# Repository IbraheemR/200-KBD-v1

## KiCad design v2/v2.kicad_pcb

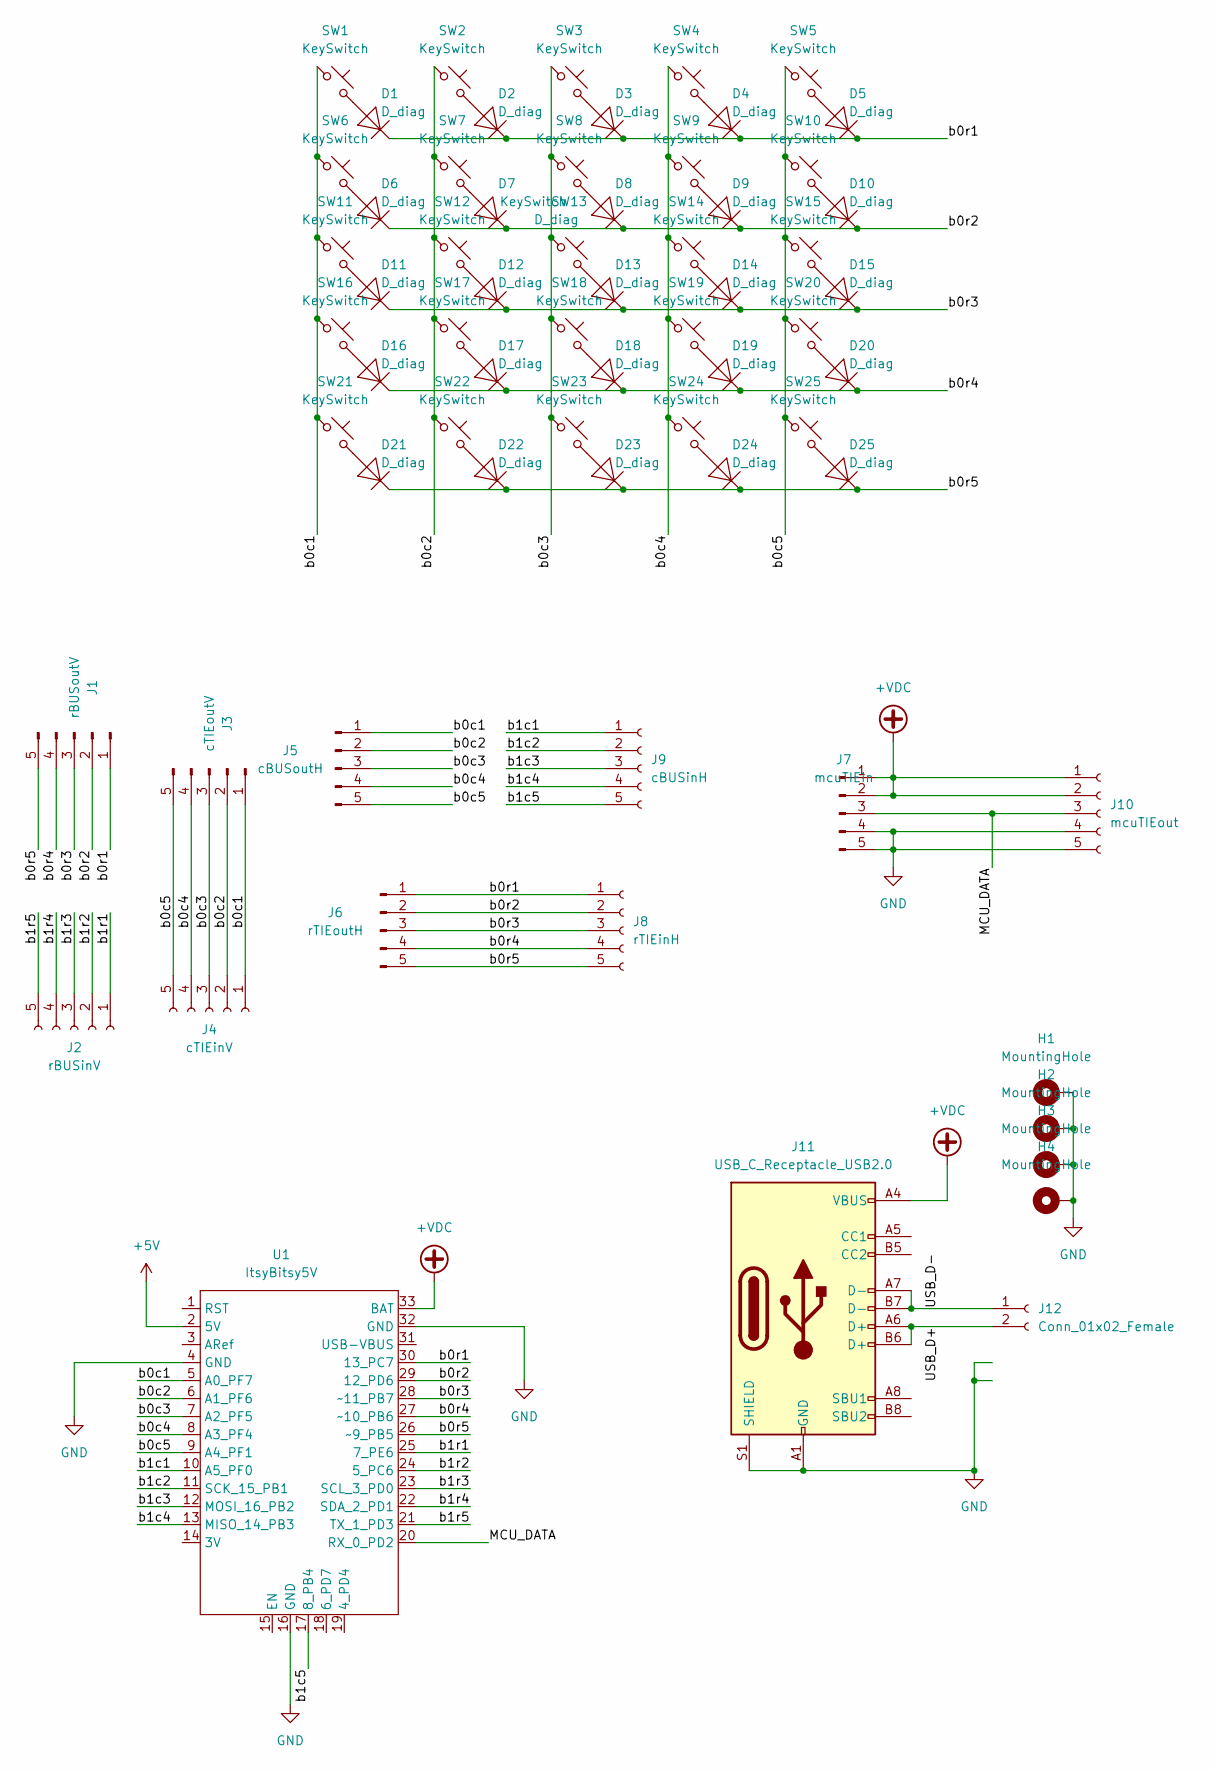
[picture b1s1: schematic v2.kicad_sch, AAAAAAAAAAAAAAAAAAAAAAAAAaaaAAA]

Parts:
D1, D2, D3, D4, D5, D6, D7, D8, D9, D10, D11, D12, D13, D14, D15, D16, D17, D18, D19, D20, D21, D22, D23, D24, D25: D_diag; D_SOD-123_NoSilk
H1, H2, H3, H4: MountingHole; MountingHole_Screw_2.5mm
J1: rBUSoutV; DumbEdgeConnectorHorizontal
J2: rBUSinV; DumbEdgeConnectorHorizontal
J3: cTIEoutV; DumbEdgeConnectorHorizontal
J4: cTIEinV; DumbEdgeConnectorHorizontal
J5: cBUSoutH; DumbEdgeConnectorVertical
J6: rTIEoutH; DumbEdgeConnectorVertical
J7: mcuTIEin; DumbEdgeConnectorVertical
J8: rTIEinH; DumbEdgeConnectorVertical
J9: cBUSinH; DumbEdgeConnectorVertical
J10: mcuTIEout; DumbEdgeConnectorVertical
J11: USB_C_Receptacle_USB2.0; USB_C_Receptacle_XKB_U262-16XN-4BVC11_NoSilk
J12: Conn_01x02_Female; USB_JUMP_PAD
SW1, SW2, SW3, SW4, SW5, SW6, SW7, SW8, SW9, SW10, SW11, SW12, SW13, SW14, SW15, SW16, SW17, SW18, SW19, SW20, SW21, SW22, SW23, SW24, SW25: KeySwitch; GateronLowProfileKeyswitch
U1: ItsyBitsy5V; ItsyBitsy

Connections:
+5V: U1.2 (5V)
+VDC: J7.1, J7.2, J10.1, J10.2, J11.A4 (VBUS), J11.A9 (VBUS), J11.B4 (VBUS), J11.B9 (VBUS), U1.33 (BAT)
/MCU_DATA: J7.3, J10.3, U1.20 (RX_0_PD2)
/USB_D+: J11.A6 (D+), J11.B6 (D+), J12.2
/USB_D-: J11.A7 (D-), J11.B7 (D-), J12.1
/b0c1: J3.1, J4.1, J5.1, SW1.1, SW6.1, SW11.1, SW16.1, SW21.1, U1.5 (A0_PF7)
/b0c2: J3.2, J4.2, J5.2, SW2.1, SW7.1, SW12.1, SW17.1, SW22.1, U1.6 (A1_PF6)
/b0c3: J3.3, J4.3, J5.3, SW3.1, SW8.1, SW13.1, SW18.1, SW23.1, U1.7 (A2_PF5)
/b0c4: J3.4, J4.4, J5.4, SW4.1, SW9.1, SW14.1, SW19.1, SW24.1, U1.8 (A3_PF4)
/b0c5: J3.5, J4.5, J5.5, SW5.1, SW10.1, SW15.1, SW20.1, SW25.1, U1.9 (A4_PF1)
/b0r1: D1.2, D2.2, D3.2, D4.2, D5.2, J1.1, J6.1, J8.1, U1.30 (13_PC7)
/b0r2: D6.2, D7.2, D8.2, D9.2, D10.2, J1.2, J6.2, J8.2, U1.29 (12_PD6)
/b0r3: D11.2, D12.2, D13.2, D14.2, D15.2, J1.3, J6.3, J8.3, U1.28 (~11_PB7)
/b0r4: D16.2, D17.2, D18.2, D19.2, D20.2, J1.4, J6.4, J8.4, U1.27 (~10_PB6)
/b0r5: D21.2, D22.2, D23.2, D24.2, D25.2, J1.5, J6.5, J8.5, U1.26 (~9_PB5)
/b1c1: J9.1, U1.10 (A5_PF0)
/b1c2: J9.2, U1.11 (SCK_15_PB1)
/b1c3: J9.3, U1.12 (MOSI_16_PB2)
/b1c4: J9.4, U1.13 (MISO_14_PB3)
/b1c5: J9.5, U1.17 (8_PB4)
/b1r1: J2.1, U1.25 (7_PE6)
/b1r2: J2.2, U1.24 (5_PC6)
/b1r3: J2.3, U1.23 (SCL_3_PD0)
/b1r4: J2.4, U1.22 (SDA_2_PD1)
/b1r5: J2.5, U1.21 (TX_1_PD3)
GND: H1.1, H2.1, H3.1, H4.1, J7.4, J7.5, J10.4, J10.5, J11.A1 (GND), J11.A12 (GND), J11.B1 (GND), J11.B12 (GND), J11.S1 (SHIELD), U1.4 (GND), U1.16 (GND), U1.32 (GND)
unnamed: D1.1, SW1.2
unnamed: D2.1, SW2.2
unnamed: D3.1, SW3.2
unnamed: D4.1, SW4.2
unnamed: D5.1, SW5.2
unnamed: D6.1, SW6.2
unnamed: D7.1, SW7.2
unnamed: D8.1, SW8.2
unnamed: D9.1, SW9.2
unnamed: D10.1, SW10.2
unnamed: D11.1, SW11.2
unnamed: D12.1, SW12.2
unnamed: D13.1, SW13.2
unnamed: D14.1, SW14.2
unnamed: D15.1, SW15.2
unnamed: D16.1, SW16.2
unnamed: D17.1, SW17.2
unnamed: D18.1, SW18.2
unnamed: D19.1, SW19.2
unnamed: D20.1, SW20.2
unnamed: D21.1, SW21.2
unnamed: D22.1, SW22.2
unnamed: D23.1, SW23.2
unnamed: D24.1, SW24.2
unnamed: D25.1, SW25.2

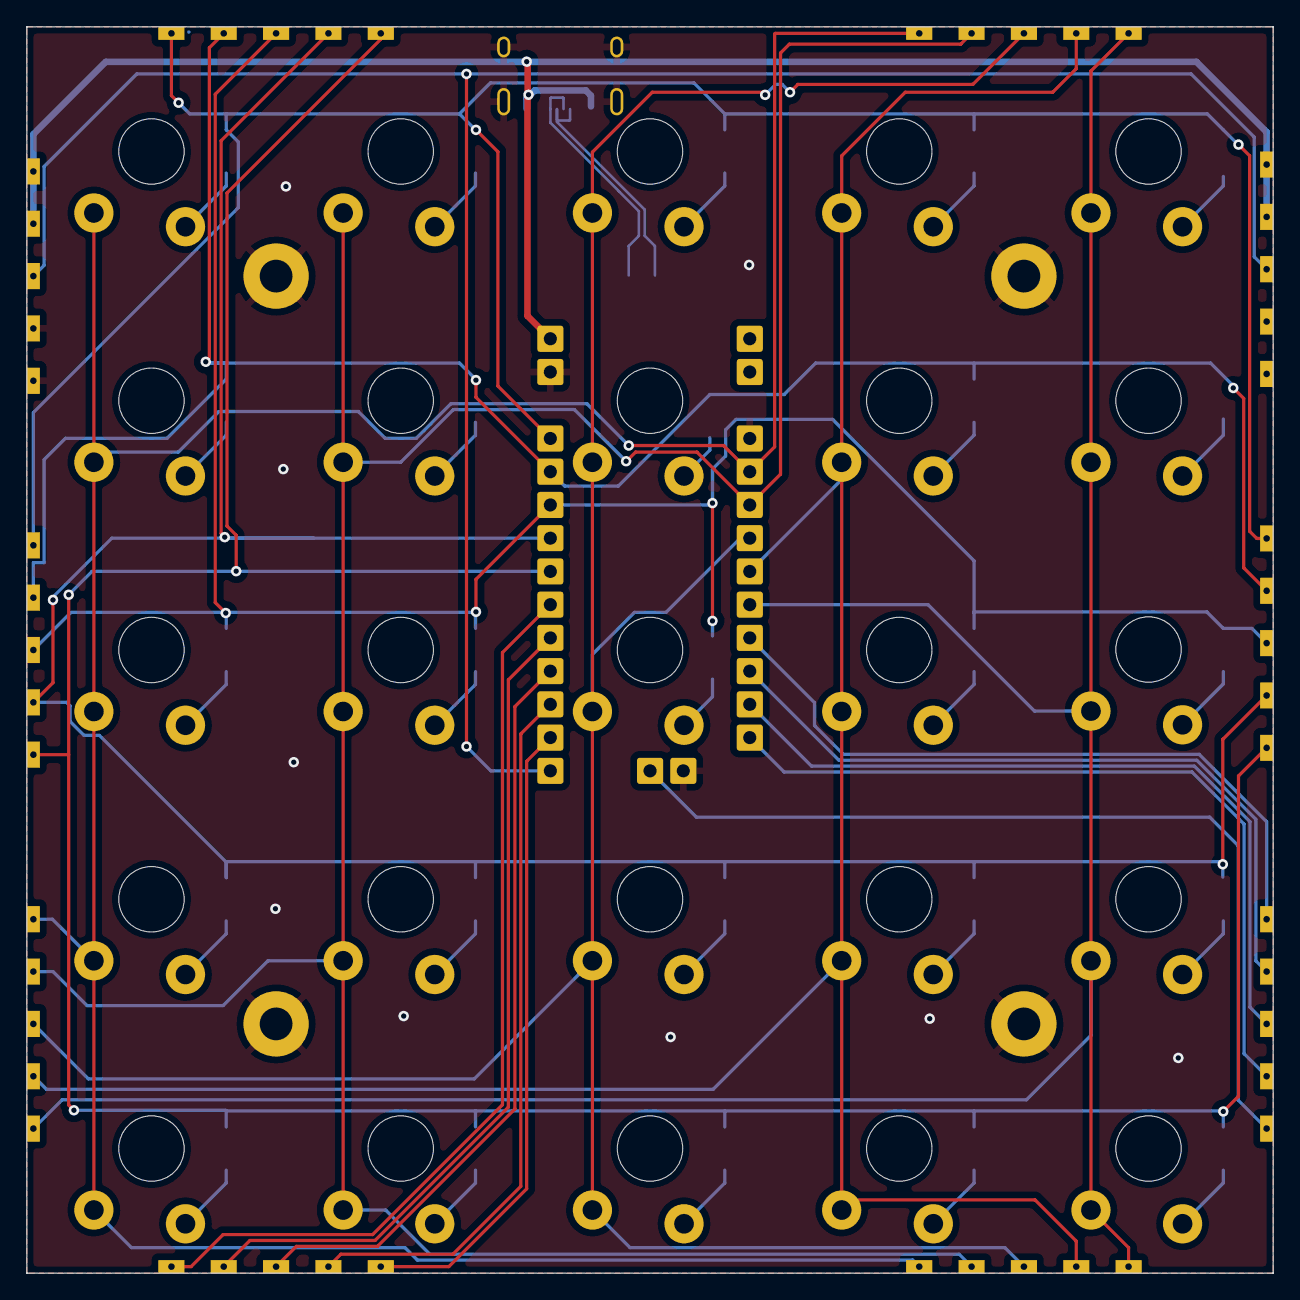
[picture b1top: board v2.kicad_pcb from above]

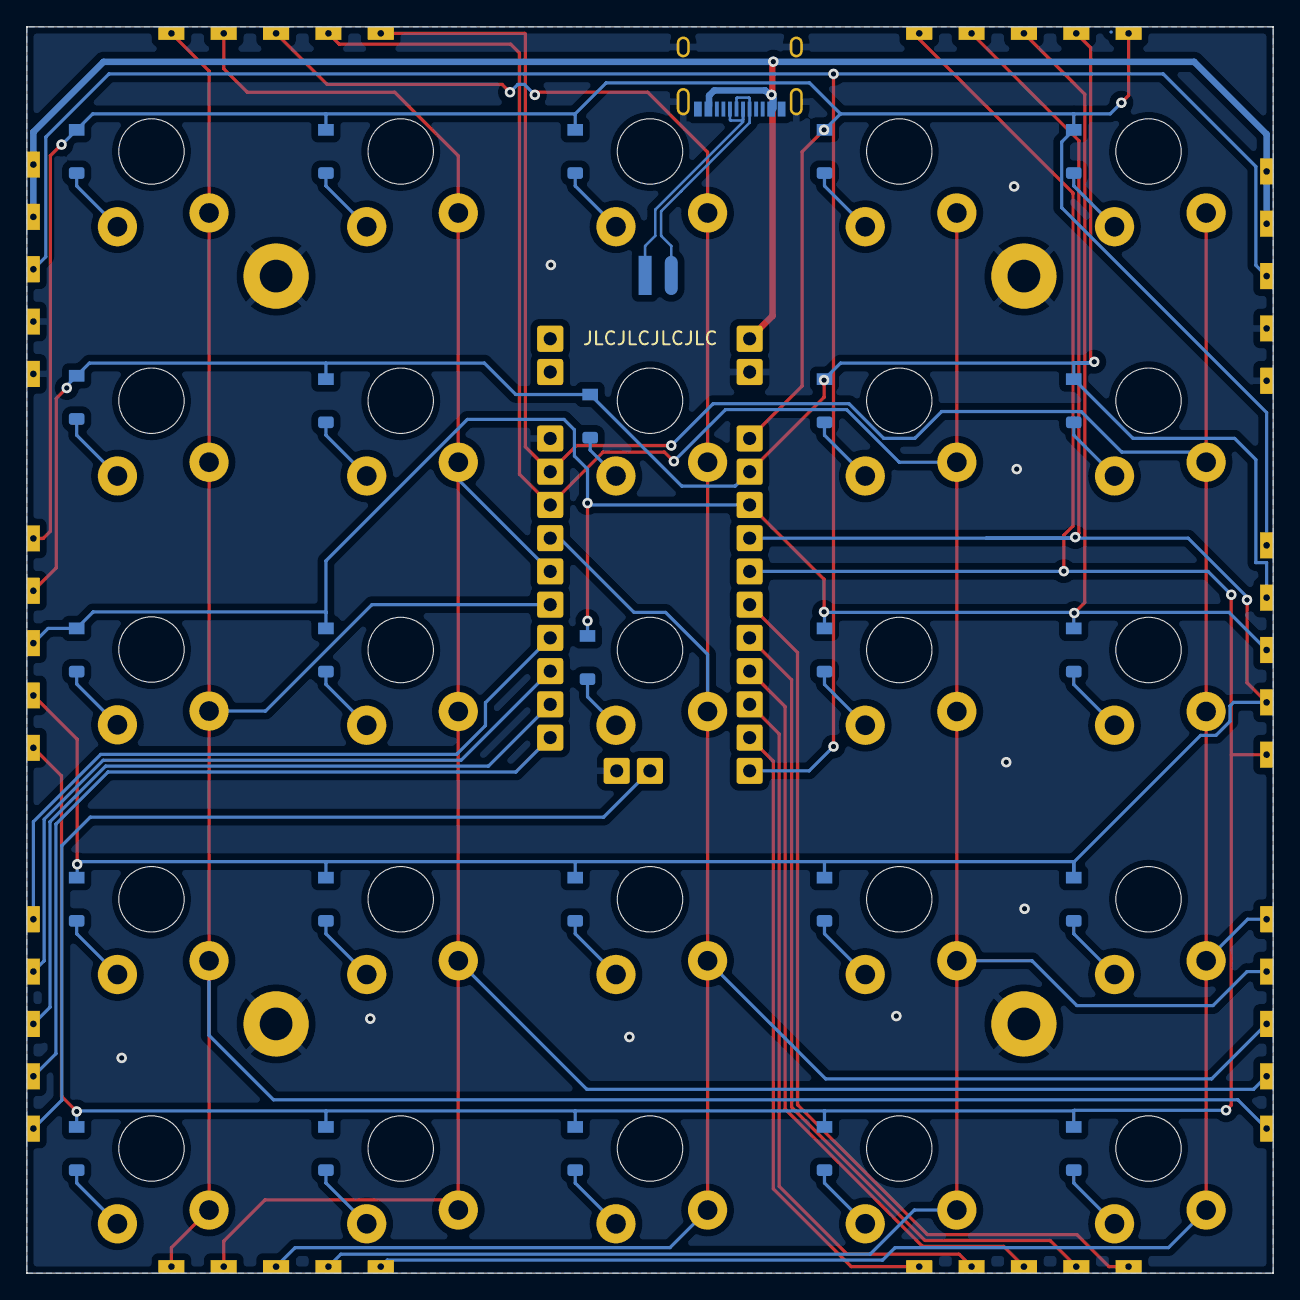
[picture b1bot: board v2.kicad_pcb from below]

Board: 2 copper layers, 95.2 x 95.2 mm, 67 parts (28 on the bottom side), 50 nets.

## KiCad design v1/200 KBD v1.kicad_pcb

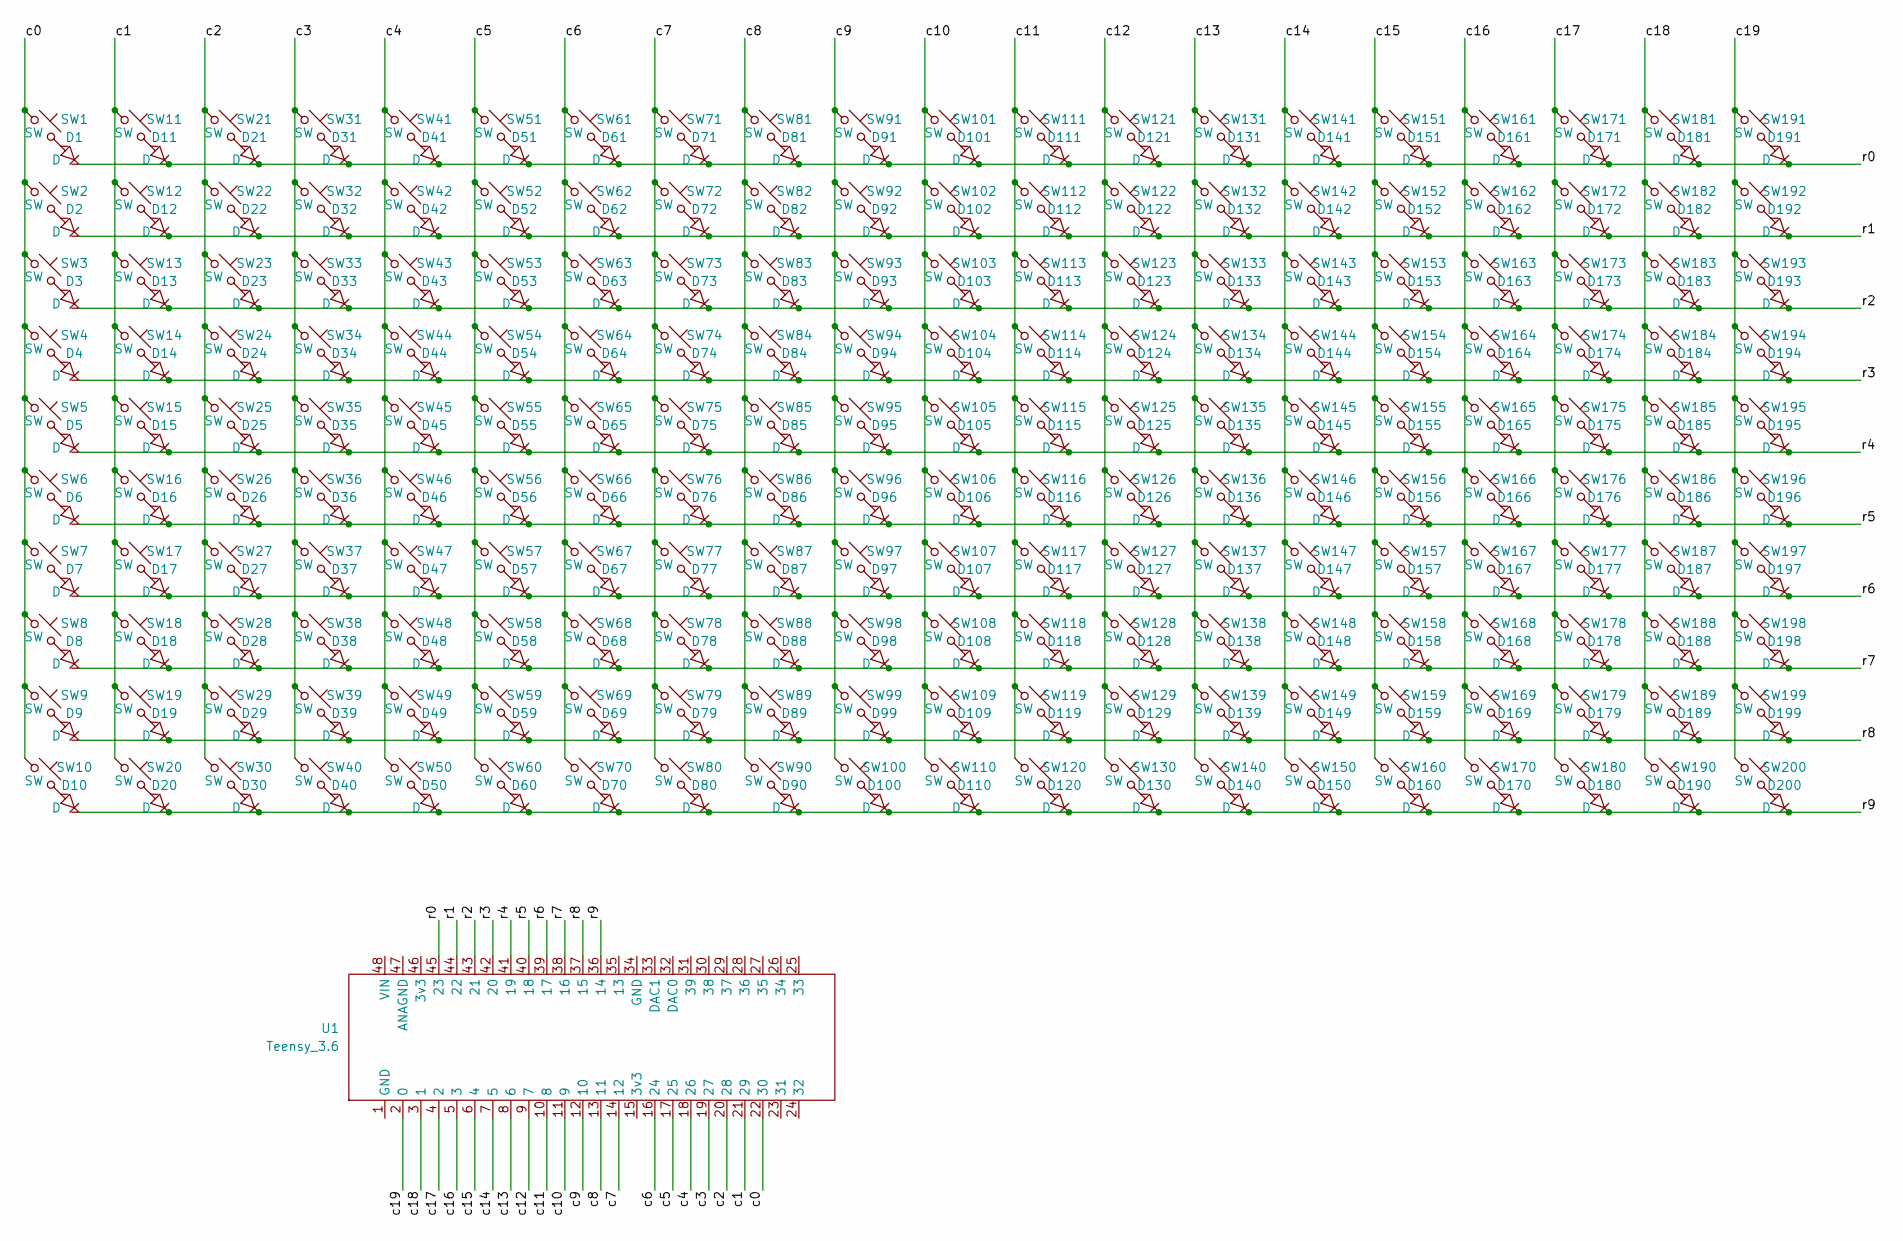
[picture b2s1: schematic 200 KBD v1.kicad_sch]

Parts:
D1, D2, D3, D4, D5, D6, D7, D8, D9, D10, D11, D12, D13, D14, D15, D16, D17, D18, D19, D20, D21, D22, D23, D24, D25, D26, D27, D28, D29, D30, D31, D32, D33, D34, D35, D36, D37, D38, D39, D40, D41, D42, D43, D44, D45, D46, D47, D48, D49, D50, D51, D52, D53, D54, D55, D56, D57, D58, D59, D60, D61, D62, D63, D64, D65, D66, D67, D68, D69, D70, D71, D72, D73, D74, D75, D76, D77, D78, D79, D80, D81, D82, D83, D84, D85, D86, D87, D88, D89, D90, D91, D92, D93, D94, D95, D96, D97, D98, D99, D100, D101, D102, D103, D104, D105, D106, D107, D108, D109, D110, D111, D112, D113, D114, D115, D116, D117, D118, D119, D120, D121, D122, D123, D124, D125, D126, D127, D128, D129, D130, D131, D132, D133, D134, D135, D136, D137, D138, D139, D140, D141, D142, D143, D144, D145, D146, D147, D148, D149, D150, D151, D152, D153, D154, D155, D156, D157, D158, D159, D160, D161, D162, D163, D164, D165, D166, D167, D168, D169, D170, D171, D172, D173, D174, D175, D176, D177, D178, D179, D180, D181, D182, D183, D184, D185, D186, D187, D188, D189, D190, D191, D192, D193, D194, D195, D196, D197, D198, D199, D200: D; D_0805_2012Metric_Pad1.15x1.40mm_HandSolder_NoSilk
SW1, SW2, SW3, SW4, SW5, SW6, SW7, SW8, SW9, SW10, SW11, SW12, SW13, SW14, SW15, SW16, SW17, SW18, SW19, SW20, SW21, SW22, SW23, SW24, SW25, SW26, SW27, SW28, SW29, SW30, SW31, SW32, SW33, SW34, SW35, SW36, SW37, SW38, SW39, SW40, SW41, SW42, SW43, SW44, SW45, SW46, SW47, SW48, SW49, SW50, SW51, SW52, SW53, SW54, SW55, SW56, SW57, SW58, SW59, SW60, SW61, SW62, SW63, SW64, SW65, SW66, SW67, SW68, SW69, SW70, SW71, SW72, SW73, SW74, SW75, SW76, SW77, SW78, SW79, SW80, SW81, SW82, SW83, SW84, SW85, SW86, SW87, SW88, SW89, SW90, SW91, SW92, SW93, SW94, SW95, SW96, SW97, SW98, SW99, SW100, SW101, SW102, SW103, SW104, SW105, SW106, SW107, SW108, SW109, SW110, SW111, SW112, SW113, SW114, SW115, SW116, SW117, SW118, SW119, SW120, SW121, SW122, SW123, SW124, SW125, SW126, SW127, SW128, SW129, SW130, SW131, SW132, SW133, SW134, SW135, SW136, SW137, SW138, SW139, SW140, SW141, SW142, SW143, SW144, SW145, SW146, SW147, SW148, SW149, SW150, SW151, SW152, SW153, SW154, SW155, SW156, SW157, SW158, SW159, SW160, SW161, SW162, SW163, SW164, SW165, SW166, SW167, SW168, SW169, SW170, SW171, SW172, SW173, SW174, SW175, SW176, SW177, SW178, SW179, SW180, SW181, SW182, SW183, SW184, SW185, SW186, SW187, SW188, SW189, SW190, SW191, SW192, SW193, SW194, SW195, SW196, SW197, SW198, SW199, SW200: SW; SW_Cherry_MX_1.00u_PCB_Alt_Origin
U1: Teensy_3.6; Teensy 3.6

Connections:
/c0: SW1.1, SW2.1, SW3.1, SW4.1, SW5.1, SW6.1, SW7.1, SW8.1, SW9.1, SW10.1, U1.22 (30)
/c1: SW11.1, SW12.1, SW13.1, SW14.1, SW15.1, SW16.1, SW17.1, SW18.1, SW19.1, SW20.1, U1.21 (29)
/c2: SW21.1, SW22.1, SW23.1, SW24.1, SW25.1, SW26.1, SW27.1, SW28.1, SW29.1, SW30.1, U1.20 (28)
/c3: SW31.1, SW32.1, SW33.1, SW34.1, SW35.1, SW36.1, SW37.1, SW38.1, SW39.1, SW40.1, U1.19 (27)
/c4: SW41.1, SW42.1, SW43.1, SW44.1, SW45.1, SW46.1, SW47.1, SW48.1, SW49.1, SW50.1, U1.18 (26)
/c5: SW51.1, SW52.1, SW53.1, SW54.1, SW55.1, SW56.1, SW57.1, SW58.1, SW59.1, SW60.1, U1.17 (25)
/c6: SW61.1, SW62.1, SW63.1, SW64.1, SW65.1, SW66.1, SW67.1, SW68.1, SW69.1, SW70.1, U1.16 (24)
/c7: SW71.1, SW72.1, SW73.1, SW74.1, SW75.1, SW76.1, SW77.1, SW78.1, SW79.1, SW80.1, U1.14 (12)
/c8: SW81.1, SW82.1, SW83.1, SW84.1, SW85.1, SW86.1, SW87.1, SW88.1, SW89.1, SW90.1, U1.13 (11)
/c9: SW91.1, SW92.1, SW93.1, SW94.1, SW95.1, SW96.1, SW97.1, SW98.1, SW99.1, SW100.1, U1.12 (10)
/c10: SW101.1, SW102.1, SW103.1, SW104.1, SW105.1, SW106.1, SW107.1, SW108.1, SW109.1, SW110.1, U1.11 (9)
/c11: SW111.1, SW112.1, SW113.1, SW114.1, SW115.1, SW116.1, SW117.1, SW118.1, SW119.1, SW120.1, U1.10 (8)
/c12: SW121.1, SW122.1, SW123.1, SW124.1, SW125.1, SW126.1, SW127.1, SW128.1, SW129.1, SW130.1, U1.9 (7)
/c13: SW131.1, SW132.1, SW133.1, SW134.1, SW135.1, SW136.1, SW137.1, SW138.1, SW139.1, SW140.1, U1.8 (6)
/c14: SW141.1, SW142.1, SW143.1, SW144.1, SW145.1, SW146.1, SW147.1, SW148.1, SW149.1, SW150.1, U1.7 (5)
/c15: SW151.1, SW152.1, SW153.1, SW154.1, SW155.1, SW156.1, SW157.1, SW158.1, SW159.1, SW160.1, U1.6 (4)
/c16: SW161.1, SW162.1, SW163.1, SW164.1, SW165.1, SW166.1, SW167.1, SW168.1, SW169.1, SW170.1, U1.5 (3)
/c17: SW171.1, SW172.1, SW173.1, SW174.1, SW175.1, SW176.1, SW177.1, SW178.1, SW179.1, SW180.1, U1.4 (2)
/c18: SW181.1, SW182.1, SW183.1, SW184.1, SW185.1, SW186.1, SW187.1, SW188.1, SW189.1, SW190.1, U1.3 (1)
/c19: SW191.1, SW192.1, SW193.1, SW194.1, SW195.1, SW196.1, SW197.1, SW198.1, SW199.1, SW200.1, U1.2 (0)
/r0: D1.2, D11.2, D21.2, D31.2, D41.2, D51.2, D61.2, D71.2, D81.2, D91.2, D101.2, D111.2, D121.2, D131.2, D141.2, D151.2, D161.2, D171.2, D181.2, D191.2, U1.45 (23)
/r1: D2.2, D12.2, D22.2, D32.2, D42.2, D52.2, D62.2, D72.2, D82.2, D92.2, D102.2, D112.2, D122.2, D132.2, D142.2, D152.2, D162.2, D172.2, D182.2, D192.2, U1.44 (22)
/r2: D3.2, D13.2, D23.2, D33.2, D43.2, D53.2, D63.2, D73.2, D83.2, D93.2, D103.2, D113.2, D123.2, D133.2, D143.2, D153.2, D163.2, D173.2, D183.2, D193.2, U1.43 (21)
/r3: D4.2, D14.2, D24.2, D34.2, D44.2, D54.2, D64.2, D74.2, D84.2, D94.2, D104.2, D114.2, D124.2, D134.2, D144.2, D154.2, D164.2, D174.2, D184.2, D194.2, U1.42 (20)
/r4: D5.2, D15.2, D25.2, D35.2, D45.2, D55.2, D65.2, D75.2, D85.2, D95.2, D105.2, D115.2, D125.2, D135.2, D145.2, D155.2, D165.2, D175.2, D185.2, D195.2, U1.41 (19)
/r5: D6.2, D16.2, D26.2, D36.2, D46.2, D56.2, D66.2, D76.2, D86.2, D96.2, D106.2, D116.2, D126.2, D136.2, D146.2, D156.2, D166.2, D176.2, D186.2, D196.2, U1.40 (18)
/r6: D7.2, D17.2, D27.2, D37.2, D47.2, D57.2, D67.2, D77.2, D87.2, D97.2, D107.2, D117.2, D127.2, D137.2, D147.2, D157.2, D167.2, D177.2, D187.2, D197.2, U1.39 (17)
/r7: D8.2, D18.2, D28.2, D38.2, D48.2, D58.2, D68.2, D78.2, D88.2, D98.2, D108.2, D118.2, D128.2, D138.2, D148.2, D158.2, D168.2, D178.2, D188.2, D198.2, U1.38 (16)
/r8: D9.2, D19.2, D29.2, D39.2, D49.2, D59.2, D69.2, D79.2, D89.2, D99.2, D109.2, D119.2, D129.2, D139.2, D149.2, D159.2, D169.2, D179.2, D189.2, D199.2, U1.37 (15)
/r9: D10.2, D20.2, D30.2, D40.2, D50.2, D60.2, D70.2, D80.2, D90.2, D100.2, D110.2, D120.2, D130.2, D140.2, D150.2, D160.2, D170.2, D180.2, D190.2, D200.2, U1.36 (14)
unnamed: D1.1, SW1.2
unnamed: D2.1, SW2.2
unnamed: D3.1, SW3.2
unnamed: D4.1, SW4.2
unnamed: D5.1, SW5.2
unnamed: D6.1, SW6.2
unnamed: D7.1, SW7.2
unnamed: D8.1, SW8.2
unnamed: D9.1, SW9.2
unnamed: D10.1, SW10.2
unnamed: D11.1, SW11.2
unnamed: D12.1, SW12.2
unnamed: D13.1, SW13.2
unnamed: D14.1, SW14.2
unnamed: D15.1, SW15.2
unnamed: D16.1, SW16.2
unnamed: D17.1, SW17.2
unnamed: D18.1, SW18.2
unnamed: D19.1, SW19.2
unnamed: D20.1, SW20.2
unnamed: D21.1, SW21.2
unnamed: D22.1, SW22.2
unnamed: D23.1, SW23.2
unnamed: D24.1, SW24.2
unnamed: D25.1, SW25.2
unnamed: D26.1, SW26.2
unnamed: D27.1, SW27.2
unnamed: D28.1, SW28.2
unnamed: D29.1, SW29.2
unnamed: D30.1, SW30.2
unnamed: D31.1, SW31.2
unnamed: D32.1, SW32.2
unnamed: D33.1, SW33.2
unnamed: D34.1, SW34.2
unnamed: D35.1, SW35.2
unnamed: D36.1, SW36.2
unnamed: D37.1, SW37.2
unnamed: D38.1, SW38.2
unnamed: D39.1, SW39.2
unnamed: D40.1, SW40.2
unnamed: D41.1, SW41.2
unnamed: D42.1, SW42.2
unnamed: D43.1, SW43.2
unnamed: D44.1, SW44.2
unnamed: D45.1, SW45.2
unnamed: D46.1, SW46.2
unnamed: D47.1, SW47.2
unnamed: D48.1, SW48.2
unnamed: D49.1, SW49.2
unnamed: D50.1, SW50.2
unnamed: D51.1, SW51.2
unnamed: D52.1, SW52.2
unnamed: D53.1, SW53.2
unnamed: D54.1, SW54.2
unnamed: D55.1, SW55.2
unnamed: D56.1, SW56.2
unnamed: D57.1, SW57.2
unnamed: D58.1, SW58.2
unnamed: D59.1, SW59.2
unnamed: D60.1, SW60.2
unnamed: D61.1, SW61.2
unnamed: D62.1, SW62.2
unnamed: D63.1, SW63.2
unnamed: D64.1, SW64.2
unnamed: D65.1, SW65.2
unnamed: D66.1, SW66.2
unnamed: D67.1, SW67.2
unnamed: D68.1, SW68.2
unnamed: D69.1, SW69.2
unnamed: D70.1, SW70.2
unnamed: D71.1, SW71.2
unnamed: D72.1, SW72.2
unnamed: D73.1, SW73.2
unnamed: D74.1, SW74.2
unnamed: D75.1, SW75.2
unnamed: D76.1, SW76.2
unnamed: D77.1, SW77.2
unnamed: D78.1, SW78.2
unnamed: D79.1, SW79.2
unnamed: D80.1, SW80.2
unnamed: D81.1, SW81.2
unnamed: D82.1, SW82.2
unnamed: D83.1, SW83.2
unnamed: D84.1, SW84.2
unnamed: D85.1, SW85.2
unnamed: D86.1, SW86.2
unnamed: D87.1, SW87.2
unnamed: D88.1, SW88.2
unnamed: D89.1, SW89.2
unnamed: D90.1, SW90.2
unnamed: D91.1, SW91.2
unnamed: D92.1, SW92.2
unnamed: D93.1, SW93.2
unnamed: D94.1, SW94.2
unnamed: D95.1, SW95.2
unnamed: D96.1, SW96.2
unnamed: D97.1, SW97.2
unnamed: D98.1, SW98.2
unnamed: D99.1, SW99.2
unnamed: D100.1, SW100.2
unnamed: D101.1, SW101.2
unnamed: D102.1, SW102.2
unnamed: D103.1, SW103.2
unnamed: D104.1, SW104.2
unnamed: D105.1, SW105.2
unnamed: D106.1, SW106.2
unnamed: D107.1, SW107.2
unnamed: D108.1, SW108.2
unnamed: D109.1, SW109.2
unnamed: D110.1, SW110.2
unnamed: D111.1, SW111.2
unnamed: D112.1, SW112.2
unnamed: D113.1, SW113.2
unnamed: D114.1, SW114.2
unnamed: D115.1, SW115.2
unnamed: D116.1, SW116.2
unnamed: D117.1, SW117.2
unnamed: D118.1, SW118.2
unnamed: D119.1, SW119.2
unnamed: D120.1, SW120.2
unnamed: D121.1, SW121.2
unnamed: D122.1, SW122.2
unnamed: D123.1, SW123.2
unnamed: D124.1, SW124.2
unnamed: D125.1, SW125.2
unnamed: D126.1, SW126.2
unnamed: D127.1, SW127.2
unnamed: D128.1, SW128.2
unnamed: D129.1, SW129.2
unnamed: D130.1, SW130.2
unnamed: D131.1, SW131.2
unnamed: D132.1, SW132.2
unnamed: D133.1, SW133.2
unnamed: D134.1, SW134.2
unnamed: D135.1, SW135.2
unnamed: D136.1, SW136.2
unnamed: D137.1, SW137.2
unnamed: D138.1, SW138.2
unnamed: D139.1, SW139.2
unnamed: D140.1, SW140.2
unnamed: D141.1, SW141.2
unnamed: D142.1, SW142.2
unnamed: D143.1, SW143.2
unnamed: D144.1, SW144.2
unnamed: D145.1, SW145.2
unnamed: D146.1, SW146.2
unnamed: D147.1, SW147.2
unnamed: D148.1, SW148.2
unnamed: D149.1, SW149.2
unnamed: D150.1, SW150.2
unnamed: D151.1, SW151.2
unnamed: D152.1, SW152.2
unnamed: D153.1, SW153.2
unnamed: D154.1, SW154.2
unnamed: D155.1, SW155.2
unnamed: D156.1, SW156.2
unnamed: D157.1, SW157.2
unnamed: D158.1, SW158.2
unnamed: D159.1, SW159.2
unnamed: D160.1, SW160.2
unnamed: D161.1, SW161.2
unnamed: D162.1, SW162.2
unnamed: D163.1, SW163.2
unnamed: D164.1, SW164.2
unnamed: D165.1, SW165.2
unnamed: D166.1, SW166.2
unnamed: D167.1, SW167.2
unnamed: D168.1, SW168.2
unnamed: D169.1, SW169.2
unnamed: D170.1, SW170.2
unnamed: D171.1, SW171.2
unnamed: D172.1, SW172.2
unnamed: D173.1, SW173.2
unnamed: D174.1, SW174.2
unnamed: D175.1, SW175.2
unnamed: D176.1, SW176.2
unnamed: D177.1, SW177.2
unnamed: D178.1, SW178.2
unnamed: D179.1, SW179.2
unnamed: D180.1, SW180.2
unnamed: D181.1, SW181.2
unnamed: D182.1, SW182.2
unnamed: D183.1, SW183.2
unnamed: D184.1, SW184.2
unnamed: D185.1, SW185.2
unnamed: D186.1, SW186.2
unnamed: D187.1, SW187.2
unnamed: D188.1, SW188.2
unnamed: D189.1, SW189.2
unnamed: D190.1, SW190.2
unnamed: D191.1, SW191.2
unnamed: D192.1, SW192.2
unnamed: D193.1, SW193.2
unnamed: D194.1, SW194.2
unnamed: D195.1, SW195.2
unnamed: D196.1, SW196.2
unnamed: D197.1, SW197.2
unnamed: D198.1, SW198.2
unnamed: D199.1, SW199.2
unnamed: D200.1, SW200.2

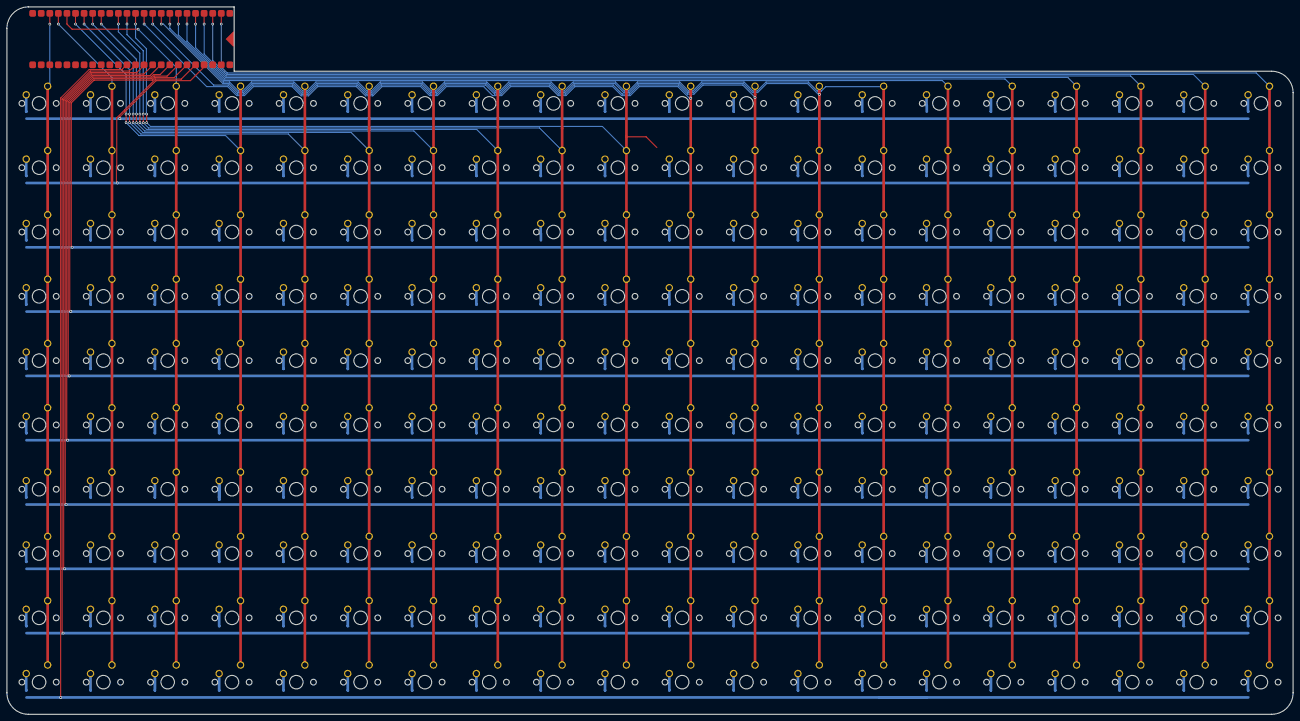
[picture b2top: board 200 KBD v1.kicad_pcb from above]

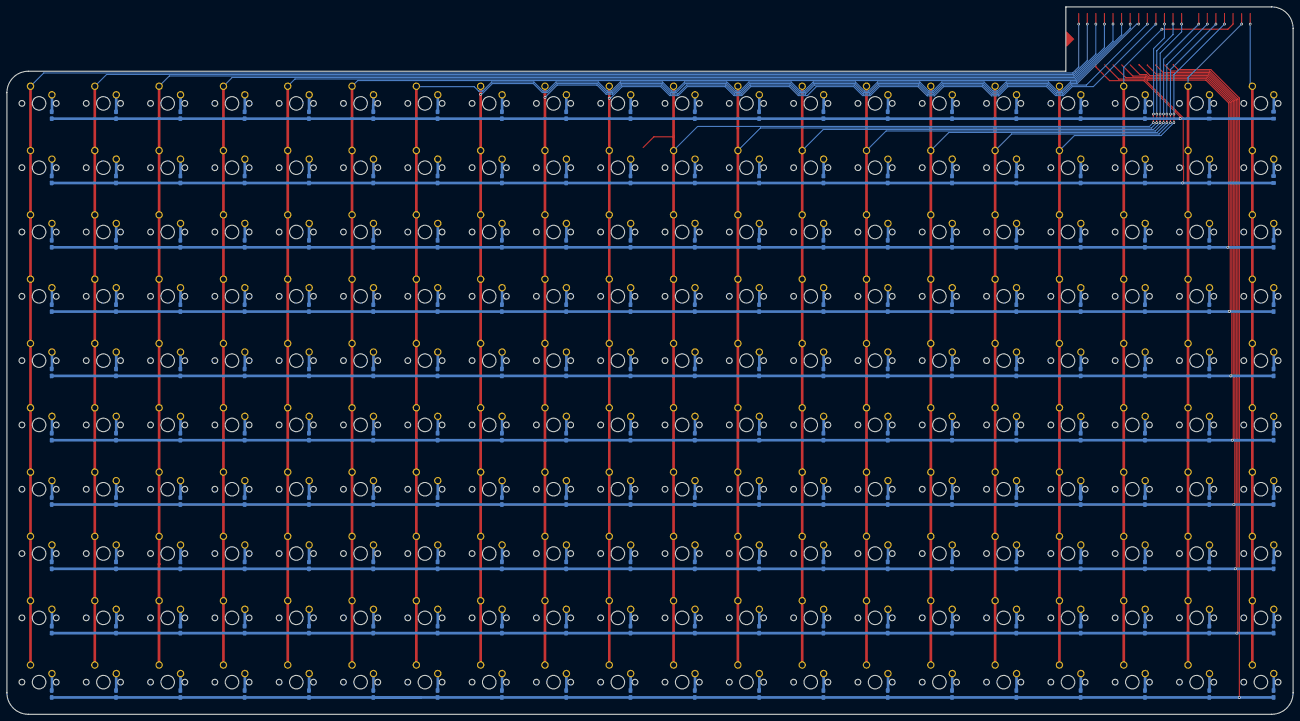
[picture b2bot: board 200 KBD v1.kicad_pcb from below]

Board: 2 copper layers, 381.0 x 209.6 mm, 401 parts (200 on the bottom side), 230 nets.

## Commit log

2022-03-27 Reorganise & begin v2 tiled board system
2022-03-28 Finish v2 keyboard tile
2022-03-28 Change diode to SOD-123, some tweaks
2022-03-28 Fix key order & run DRC
2022-04-01 Refactor to include USB
2022-04-02 Fix connection error in BUSs & TIEs
2022-04-03 Tweaks & Cleanup
2022-04-06 Add mounting holes, tweak gound plane
2022-05-04 Optimise and reroute after first order feedback. Also add ordered files archive.
